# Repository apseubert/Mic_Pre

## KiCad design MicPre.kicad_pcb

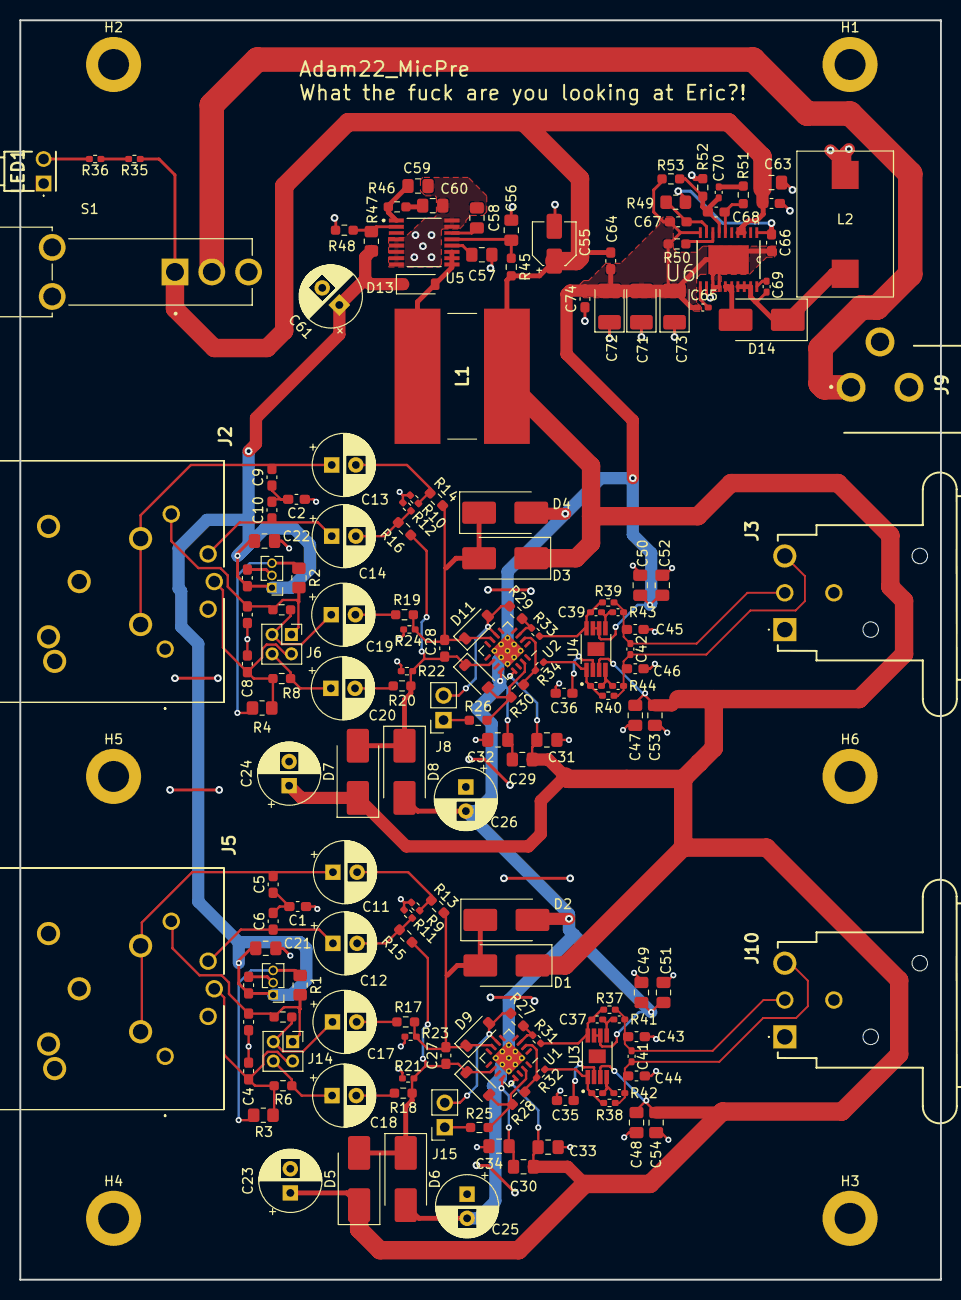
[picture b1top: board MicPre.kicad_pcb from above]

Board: 2 copper layers, 95.2 x 130.3 mm, 168 parts (0 on the bottom side), 74 nets.

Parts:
C1, C2, C3, C4, C5, C6, C7, C8, C9, C10, C15, C16, C27, C28, C35, C36, C43, C44, C45, C46: 100pf; C_0603_1608Metric_Pad1.08x0.95mm_HandSolder
C11, C12, C13, C14, C17, C18, C19, C20, C23, C24, C25, C26, C61: 47u, 63V; CP_Radial_D6.3mm_P2.50mm
C21, C22, C51, C52, C53, C54: 10uF; C_0805_2012Metric_Pad1.18x1.45mm_HandSolder
C29, C30, C31, C32, C33, C34, C47, C48, C49, C50, C63: 0.1uF; C_0805_2012Metric_Pad1.18x1.45mm_HandSolder
C37, C38, C39, C40: 1nF; C_0402_1005Metric_Pad0.74x0.62mm_HandSolder
C41, C42: 2.7nF; C_0402_1005Metric_Pad0.74x0.62mm_HandSolder
C55: 2.2uF, 50V; CP_Elec_4x3.9
C56, C57: 100nF; C_0805_2012Metric_Pad1.18x1.45mm_HandSolder
C58: 10nF; C_0805_2012Metric_Pad1.18x1.45mm_HandSolder
C59: 100pF; C_0805_2012Metric_Pad1.18x1.45mm_HandSolder
C60: 3.3nF; C_0805_2012Metric_Pad1.18x1.45mm_HandSolder
C62, C64, C66: 1uF; C_0603_1608Metric_Pad1.08x0.95mm_HandSolder
C65: 33nF; C_0402_1005Metric_Pad0.74x0.62mm_HandSolder
C67: 120pF; C_0603_1608Metric_Pad1.08x0.95mm_HandSolder
C68: 6.8pF; C_0603_1608Metric_Pad1.08x0.95mm_HandSolder
C69: 22nF; C_0402_1005Metric_Pad0.74x0.62mm_HandSolder
C70: 680pF; C_0402_1005Metric_Pad0.74x0.62mm_HandSolder
C71, C72, C73: 15uF; CP_EIA-3528-15_AVX-H_Pad1.50x2.35mm_HandSolder
C74: 2.2uF; C_0603_1608Metric_Pad1.08x0.95mm_HandSolder
D1, D2, D3, D4, D5, D6, D7, D8: 1N4934; D_SMB_Handsoldering
D9, D10, D11, D12: 1N4148; D_SOD-123
D13: 1V, 150mA; D_SOD-123
D14: 700mV, 5A; D_SMB_Handsoldering
H1, H2, H3, H4, H5, H6: MountingHole; MountingHole_3.2mm_M3_ISO7380_Pad
J2, J5: NCJ6FA-H-0; NCJ6FAH0
J3, J10: NC3MAAH
J4, J7: Conn_01x03_Male; PinHeader_1x03_P1.27mm_Vertical
J6, J14: Conn_01x04; PinSocket_2x02_P2.00mm_Vertical
J8, J15: Conn_01x02; PinSocket_1x02_P2.54mm_Vertical
J9: PJ-102BH; PJ-102AH
L1: 270uH; SDR1307100ML
L2: 15uH; ‎P0751.153NLT
LED1: 551-1309F; 5511309F
R1, R2, R3, R4: 6.81k; R_0805_2012Metric_Pad1.20x1.40mm_HandSolder
R5, R6, R7, R8: 1.1k; R_0603_1608Metric_Pad0.98x0.95mm_HandSolder
R9, R10, R11, R12: 47k; R_0402_1005Metric_Pad0.72x0.64mm_HandSolder
R13, R14, R15, R16, R48: 11k; R_0603_1608Metric_Pad0.98x0.95mm_HandSolder
R17, R18, R19, R20, R25, R26, R45: 10R; R_0603_1608Metric_Pad0.98x0.95mm_HandSolder
R21, R22, R23, R24, R35, R36: 1.2k; R_0402_1005Metric_Pad0.72x0.64mm_HandSolder
R27, R28, R29, R30: 5k; R_0603_1608Metric_Pad0.98x0.95mm_HandSolder
R31, R32, R33, R34, R37, R38, R39, R40: 390; R_0402_1005Metric_Pad0.72x0.64mm_HandSolder
R41, R42, R43, R44: 49R9; C_0402_1005Metric_Pad0.74x0.62mm_HandSolder
R46: 20k; R_0603_1608Metric_Pad0.98x0.95mm_HandSolder
R47: 374k; R_0805_2012Metric_Pad1.20x1.40mm_HandSolder
R49: 200k; R_0805_2012Metric_Pad1.20x1.40mm_HandSolder
R50: 9.09k; R_0603_1608Metric_Pad0.98x0.95mm_HandSolder
R51: 88.7k; R_0603_1608Metric_Pad0.98x0.95mm_HandSolder
R52: 14.7k; R_0603_1608Metric_Pad0.98x0.95mm_HandSolder
R53: 1.65k; R_0603_1608Metric_Pad0.98x0.95mm_HandSolder
S1: 300SP1J1BLKM7QE; SW_300SP1J1BLKM7QE
U1, U2: THAT1580; QFN-16-1EP_4x4mm_P0.65mm_EP2.5x2.5mm_ThermalVias
U3, U4: OPA1632; SOP65P490X110-9N
U5: LM5000-3MTCX; SOP65P640X120-16N
U6: LM25576QMH; SOP65P640X110-21N

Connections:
+12V: C23.1, C24.1, C29.2, C30.2, C31.2, C33.2, C47.2, C48.2, C53.1, C54.1, C55.1, C62.1, C63.1, C64.1, D1.1 (K), D3.1 (K), D5.1 (K), D7.1 (K), L1.1, R35.1, R45.2, S1.1, U1.13 (V+), U2.13 (V+), U3.3 (+), U4.3 (+), U6.3 (VIN_2), U6.4 (VIN)
+48V: C15.2, C16.2, C21.1, C22.1, C61.1, D13.1 (K), J4.1, J7.1, R47.2
-12V: C25.2, C26.2, C29.1, C30.1, C32.2, C34.2, C49.2, C50.2, C51.1, C52.1, C64.2, C65.2, C66.2, C67.2, C71.2, C72.2, C73.2, C74.2, D2.2 (A), D4.2 (A), D6.2 (A), D8.2 (A), R50.2, R53.2, U1.12 (V-), U1.17 (V-), U2.12 (V-), U2.17 (V-), U3.6 (-), U3.7 (EN), U4.6 (-), U4.7 (EN), U6.10 (AGND), U6.13 (PGND_2), U6.14 (PGND), U6.21 (EPAD)
/Mic Lane 1/20dB_Pad1: C8.2, J2.3, J6.3, R4.2, R8.1
/Mic Lane 1/Mic1_Vout+: C42.2, C46.2, J3.2, R40.2, R44.2
/Mic Lane 1/Mic1_Vout-: C42.1, C45.1, J3.3, R39.2, R43.2
/Mic Lane 2/20dB_Pad1: C4.2, J5.3, J14.3, R3.2, R6.1
/Mic Lane 2/Mic1_Vout+: C41.2, C44.2, J10.2, R38.2, R42.2
/Mic Lane 2/Mic1_Vout-: C41.1, C43.1, J10.3, R37.2, R41.2
Earth: C1.1, C2.1, C3.2, C4.1, C7.2, C8.1, C15.1, C16.1, C21.2, C22.2, C23.2, C24.2, C25.1, C26.1, C31.1, C32.1, C33.1, C34.1, C35.1, C36.1, C43.2, C44.1, C45.2, C46.1, C47.1, C48.1, C49.1, C50.1, C51.2, C52.2, C53.2, C54.2, C55.2, C56.2, C57.2, C58.2, C59.2, C60.2, C61.2, C62.2, C63.2, C71.1, C72.1, C73.1, C74.1, J2.1, J2.4, J2.5, J2.6, J2.G1, J2.S1, J3.1, J3.G1, J4.2, J5.1, J5.4, J5.5, J5.6, J5.G1, J5.S1, J7.2, J9.2, J9.3, J10.1, J10.G1, L2.2, LED1.1 (K_G), R9.2, R10.2, R11.2, R12.2, R21.1, R22.1, R23.2, R24.2, R48.1, R52.1, U5.4 (AGND), U5.5 (PGND-1), U5.6 (PGND), U5.7 (PGND-3), U5.8 (PGND-2), U5.15 (FS), U5.16 (TEST), U6.12 (OUT)
unnamed: C1.2, C5.1, C6.2
unnamed: C10.1, C14.1, J2.R1
unnamed: C2.2, C9.1, C10.2
unnamed: C5.2, C11.1, J5.T1, J5.T2
unnamed: C11.2, R9.1, R13.1
unnamed: C6.1, C12.1, J5.R1
unnamed: C12.2, R11.1, R15.1
unnamed: C9.2, C13.1, J2.T1, J2.T2
unnamed: C13.2, R10.1, R14.1
unnamed: C14.2, R12.1, R16.1
unnamed: C17.2, R17.1
unnamed: C18.2, R18.1
unnamed: C19.2, R19.1
unnamed: C20.2, R20.1
unnamed: C60.1, R46.2
unnamed: C70.1, R51.2
unnamed: C27.2, D1.2 (A), D2.1 (K), D9.1 (K), R13.2, R17.2, R23.1, U1.7 (IN1)
unnamed: D9.2 (A), J15.2, R27.1, U1.6 (Rg1)
unnamed: D10.2 (A), R25.2, R28.1, U1.15 (Rg2)
unnamed: C27.1, D5.2 (A), D6.1 (K), D10.1 (K), R15.2, R18.2, R21.2, U1.10 (IN2)
unnamed: D11.2 (A), J8.2, R29.1, U2.6 (Rg1)
unnamed: C28.2, D3.2 (A), D4.1 (K), D11.1 (K), R14.2, R19.2, R24.1, U2.7 (IN1)
unnamed: D12.2 (A), R26.2, R30.1, U2.15 (Rg2)
unnamed: C28.1, D7.2 (A), D8.1 (K), D12.1 (K), R16.2, R20.2, R22.2, U2.10 (IN2)
unnamed: D13.2 (A), L1.2, U5.9 (SW-1), U5.10 (SW), U5.11 (SW-2)
unnamed: D14.2 (A), U6.15 (IS_2), U6.16 (IS)
unnamed: C69.2, D14.1 (K), L2.1, U6.17 (SW_2), U6.18 (SW), U6.19 (PRE)
unnamed: J4.3, R2.1, R4.1
unnamed: C7.1, J2.2, J6.1, R2.2, R7.1
unnamed: C19.1, J6.2, R7.2
unnamed: C20.1, J6.4, R8.2
unnamed: J7.3, R1.1, R3.1
unnamed: J8.1, R26.1
unnamed: J9.1, S1.2
unnamed: C3.1, J5.2, J14.1, R1.2, R5.1
unnamed: C17.1, J14.2, R5.2
unnamed: C18.1, J14.4, R6.2
unnamed: J15.1, R25.1
unnamed: LED1.2 (A_G), R36.2
unnamed: R28.2, R32.1, U1.2
unnamed: R30.2, R34.1, U2.2
unnamed: R35.2, R36.1
unnamed: R27.2, R31.1, U1.3 (1)
unnamed: R29.2, R33.1, U2.3 (1)
unnamed: C37.1, R31.2, R37.1, U3.8 (Vin+)
unnamed: C38.1, R32.2, R38.1, U3.1 (Vin-)
unnamed: C38.2, R42.1, U3.4 (Vout+)
unnamed: C37.2, R41.1, U3.5 (Vout-)
unnamed: C39.1, R33.2, R39.1, U4.8 (Vin+)
unnamed: C40.1, R34.2, R40.1, U4.1 (Vin-)
unnamed: C40.2, R44.1, U4.4 (Vout+)
unnamed: C39.2, R43.1, U4.5 (Vout-)
unnamed: C57.1, U5.12 (BYP)
unnamed: C59.1, R46.1, U5.1 (COMP)
unnamed: R47.1, R48.2, U5.2 (FB)
unnamed: C58.1, U5.14 (SS)
unnamed: C56.1, R45.1, U5.13 (VIN)
unnamed: C69.1, U6.20 (BST)
unnamed: C68.1, R51.1, U6.6 (COMP)
unnamed: C68.2, C70.2, R52.2, R53.1, U6.7 (FB)
unnamed: C67.1, R49.2, U6.9 (RAMP)
unnamed: R50.1, U6.8 (RT)
unnamed: C65.1, U6.11 (SS)
unnamed: C66.1, R49.1, U6.1 (VCC)

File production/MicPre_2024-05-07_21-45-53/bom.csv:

Designator,Footprint,Quantity,Value,LCSC Part #
"C1, C10, C15, C16, C2, C27, C28, C3, C35, C36, C4, C43, C44, C45, C46, C5, C6, C7, C8, C9",0603,20,100pf,
"C11, C12, C13, C14, C17, C18, C19, C20, C23, C24, C25, C26, C61",CP_Radial_D6.3mm_P2.50mm,13,"47u, 63V",
"C21, C22, C51, C52, C53, C54",0805,6,10uF,
"C29, C30, C31, C32, C33, C34, C47, C48, C49, C50, C63",0805,11,0.1uF,
"C37, C38, C39, C40",0402,4,1nF,
"C41, C42",0402,2,2.7nF,
C55,CP_Elec_4x3.9,1,"2.2uF, 50V",
"C56, C57",0805,2,100nF,
C58,0805,1,10nF,
C59,0805,1,100pF,
C60,0805,1,3.3nF,
"C62, C64, C66",0603,3,1uF,
C65,0402,1,33nF,
C67,0603,1,120pF,
C68,0603,1,6.8pF,
C69,0402,1,22nF,
C70,0402,1,680pF,
"C71, C72, C73",CP_EIA-3528-15_AVX-H_Pad1.50x2.35mm_HandSolder,3,15uF,
C74,0603,1,2.2uF,
"D1, D2, D3, D4, D5, D6, D7, D8",D_SMB_Handsoldering,8,1N4934,
"D10, D11, D12, D9",D_SOD-123,4,1N4148,
D13,D_SOD-123,1,"1V, 150mA",
D14,D_SMB_Handsoldering,1,"700mV, 5A",
"H1, H2, H3, H4, H5, H6",MountingHole_3.2mm_M3_ISO7380_Pad,6,MountingHole,
"J10, J3",NC3MAAH,2,NC3MAAH,
"J14, J6",PinSocket_2x02_P2.00mm_Vertical,2,Conn_01x04,
"J15, J8",PinSocket_1x02_P2.54mm_Vertical,2,Conn_01x02,
"J2, J5",NCJ6FAH0,2,NCJ6FA-H-0,
"J4, J7",PinHeader_1x03_P1.27mm_Vertical,2,Conn_01x03_Male,
J9,PJ-102AH,1,PJ-102BH,
L1,SDR1307100ML,1,270uH,
L2,‎P0751.153NLT,1,15uH,
LED1,5511309F,1,551-1309F,
"R1, R2, R3, R4",0805,4,6.81k,
"R10, R11, R12, R9",0402,4,47k,
"R13, R14, R15, R16, R48",0603,5,11k,
"R17, R18, R19, R20, R25, R26, R45",0603,7,10R,
"R21, R22, R23, R24, R35, R36",0402,6,1.2k,
"R27, R28, R29, R30",0603,4,5k,
"R31, R32, R33, R34, R37, R38, R39, R40",0402,8,390,
"R41, R42, R43, R44",0402,4,49R9,
R46,0603,1,20k,
R47,0805,1,374k,
R49,0805,1,200k,
"R5, R6, R7, R8",0603,4,1.1k,
R50,0603,1,9.09k,
R51,0603,1,88.7k,
R52,0603,1,14.7k,
R53,0603,1,1.65k,
S1,SW_300SP1J1BLKM7QE,1,300SP1J1BLKM7QE,
"U1, U2",QFN-16-1EP_4x4mm_P0.65mm_EP2.5x2.5mm_ThermalVias,2,THAT1580,
"U3, U4",SOP65P490X110-9N,2,OPA1632,
U5,SOP65P640X120-16N,1,LM5000-3MTCX,
U6,SOP65P640X110-21N,1,LM25576QMH,LM25576QMH

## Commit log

2024-12-25 Adding kicad files
    added all files needed for kicad project and production
